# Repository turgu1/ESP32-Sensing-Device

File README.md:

# ESP32 Sensing device V2.0

## Updates

(Updated May 31, 2022)

Received the V2.0 PCBs yesterday. First modifications (Not shown on the schematic):

- Led resistors (R13, R16): 1 kOhms instead of 220 Ohms (the LEDs are way too bright).
- Thermistor 10 kOhms resistor R11 hooked to GPIO25 instead of 3.3V using a wire: To diminish thermistor heath effect on reading values, the GPIO25 is put high only at thermistor read time.

The thermistor is only used when the device is connected to an external source of power: to get an accurate 3.3v source for thermistor read-outs.

To compensate for the lack of linearity of the ESP32 A2D, a lookup table has been generated and used by the software (ESPHome). See the generator here: `software/lut_gener.ino` Pins 34 and 25 must be connected before using the generator (without the GPIO34 resistor). Must be used for each ESP32 instance (will be different for each ESP32 chip). An example of the generated table can be found here: `software/.freezer_adc_lut.h`.

An ESPHome example of use to sense a Freezer is supplied in `software/freezer.yaml`.

(Updated May 19, 2022)

The new version is ready for production. Here are the modifications from version 1.0:

- Sensors using GPIO 15 (Generic sensor), 25 (thermistor) and 27 (light sensor) migrated to GPIO 32, 34 and 35 respectively
- Added I2C interface
- Added program-controlled led
- All parts are aligned in the same direction onboard, to simplify hand soldering
- The board is 0.6mm larger

(Updated May 18, 2022)

The thermistor and photo-resistor sensors are working well. As they use GPIO 25 and 27 A2D capability (ADC2), the WiFi interface cannot be enabled at the same time the sensors are being read: the ADC2 electronics is shared with the onboard  WiFi capability. An updated version of the device is being prepared to use ADC1 GPIOs instead. (This has been corrected in version 2.0)

(Updated May 17, 2022)

All the trials are positive so far. For R1, instead of 10K, I'm using 2.7M ohms.
Remains the thermistor and photo-resistor sensors to try.

(Updated March 29, 2022)

Initial release.

## Introduction

This is a small footprint ESP32-based sensing device, with the following characteristics:

- 30x28 mm circuit board (30x40 mm with ESP32 antenna)
- Two power modes:
    - Battery (AAx2) (through external battery case)
    - External 5 Volts power support (through power-only Micro USB-B port)
- Battery level monitoring circuit
- Three Sensing ports:
    - Multi-Purpose (configurable through Resistor and Capacitor parts)
    - Thermistor (https://learn.adafruit.com/thermistor/using-a-thermistor)
    - Photoresistor (https://learn.adafruit.com/photocells/using-a-photocell)
- I2C Interface port
- External FTDI port (through a 3-pins [GND, RxD, TxD] port) (https://learn.adafruit.com/ftdi-friend)
- RST / PGM buttons
- Power LED (for external power only)
- Programmable LED
- Designed with KiCAD V6.0.5 (https://www.kicad.org)
- Public Domain

&nbsp;&nbsp;&nbsp;&nbsp;

The choice of components is related to their availability in my inventory. 

## Design Description

Looking at the schematic, you will find here the information related to each subsection present on the device. Some subsections are required, and others are optional depending on your needs.

The electronic component identifiers required for each subsection are listed inside square brackets.

### Required Subsections

- **ESP-WROOM-32** [**U1**] - This is the processor in use on the device.
- **RESET Button** [**SW2**, **R6**, **C1**] - Required to maintain the processor working and do a reset when it is required to take back the control for programming or when the device is not behaving properly.
- **PGM Button** [**SW1**, **R5**] - For programming the processor, the PGM Button must be pressed as the reset button is also pressed, and then released *after* releasing the reset button, such that the processor will be put in program loading. The FTDI interface must be connected to the computer to transmit the new program.
- **FTDI** [**D2**, **J1**] - This is the connection to an external FTDI device that allows for communication between the ESP32 processor and a development PC for program loading and debugging output. Connector's pins are labeled **G** (Ground), **R** (RxD), and **T** (TxD) relative to the ESP32 pinout: The External FTDI GND pin must be connected to **G**, the FTDI RxD pin must be connected to **T**, and the FTDI TxD pin must be connected to **R**. Power must be supplied to the board through AA batteries or an external power supply.

### Optional Subsections

- **AAx2 Battery Connector** [**J2**] - If power is to be supplied with AA batteries, the connector is required. The battery holder wires can also be directly soldered in the through-holes. Please respect the polarity (a '+' sign is present on the board to indicate the positive wire location). **Do not connect any battery if you intend to use an external power supply.**
- **External 5V Power**, [**U2**, **J6**, **D1**, **D3**, **R13**, **C2**, **C3**, **C4**, **C5**] - This is a linear 3.3V regulator circuit, only required when a DC 5 Volts power supply is used. It is expected that the power supply is using a male micro USB-B connector. **Do not implement this subsection if you intend to use batteries.**
- **Voltage Monitoring** [**Q1**, **Q2**, **R1**, **R2**, **R3**, **R4**] - This circuit will allow for reading the 3.3 V power voltage for the device through ADC1_0 internal to the ESP32. If AA batteries are used, it will allow monitoring the battery level to replace them when required. The MOSFET transistor [**Q2**] insure that the circuit will not take a load on the batteries. Must be enabled through [**Q1**] using GPIO17.
- **Generic Sensor Input** [**J3**, **R7**, **R8**, **R9**, **R10**] - This is a port to retrieve some sensor information. The four resistors must be adjusted to consider the kind of sensing to be done (pull-up, pull-down, etc.). Some resistor locations can be used for capacitors if required (e.g. adding an RC circuit). This sensor is connected to GPIO32 (ADC1_4) of the ESP32. The J3 pins are labeled 1: G (Gnd), 2: S (Signal).
- **Heat Sensor** [**J4**, **R11**] - Allow for reading the level of Heat using an external thermistor through an A2D of the processor (ADC1). This sensor is connected to GPIO34 (ADC1_6) of the ESP32. Can be used with another kind of sensor as appropriate. The J4 pins are labeled 1: G (Gnd), 2: Th (Signal).
- **Light Sensor** [**J5**, **R12**] - Allow for reading the level of Heat using an external photoresistor through an A2D of the processor (ADC1). This sensor is connected to GPIO35 (ADC1_7) of the ESP32. Can be used with another kind of sensor as appropriate. The J5 pins are labeled 1: G (Gnd), 2: Li (Signal).
- **I2C Interface** [**J7**, **R14**, **R15**] - Used to connect to external I2C devices (displays, sensors, etc). Connected to the ESP32 through GPIO21 (SDA) and GPIO22 (SCL). The J7 connector offers 3.3v and GND pins. Resistors may have to be adjusted depending on the load. The J7 Pins are labeled 1: G (ground), 2: D (SDA), 3: + (3.3v), 4: C (SCL)
- **Program Controlled LED** [**D4**, **R16**] - Could be useful for debugging purpose. Not a good idea to use it on battery-powered devices. Connected to ESP32 GPIO12. Important: Must be programmed as an output GPIO.

### Some potential issues

- The thermistor and photoresistive interfaces are exploratory. The known lack of linearity of the ESP32 A2D may have an impact on the quality of the retrieved data. See [here](https://www.e-tinkers.com/2019/10/using-a-thermistor-with-arduino-and-unexpected-esp32-adc-non-linearity/), and [here](https://rntlab.com/question/analogread-for-ntc-thermistor/) for further information.

- The Micro USB-B connector is a specific part with only 2 through-hole pins (GND and 5V). See the BOM below for purchase locations. On Amazon, there are 100, 30, and 10 pieces bundles available. A more conventional 5-pins connector may be adapted (physical tweak or modification to the board design).

- The Power LED is for use only with the external power supply and is hooked on the 5v side of the linear regulator. It could have been hooked to the 3.3v side, closer to the ESP32.

- The linear 3.3v regulator capacitors may have to be different than the one selected. In particular, on the output side, to get a better transient response, a 22uF tantalum may replace the one indicated (per the AMS1117 spec sheet).

- Using batteries to power the device: depending on the processor speed and the networking requirements at startup (WiFi, BT, BLE), the AA batteries may not be able to supply the required startup current (100 to 500 mA). Many options are possible: use larger batteries, lithium instead of alkaline, and add some capacitors (tantalum or other) at C4/C5 locations.

## Bill of Material (BOM)

| Reference(s) | Value | Footprint | Where to find |
|:------------:|:-----:|:---------:|:--------------|
| C1           | .1uF  | 0805      |               |
| C2, C5       | 10uF  | 0805      |               |
| C3, C4       | 100nF | 0805      |               |
| D1           | MBR120VLSF or equivalent | SOD-123 | [e-Radionica](https://e-radionica.com/en/schottky-diode-mbr120vlsft3g-sod123.html), [Digikey](https://www.digikey.com/en/products/detail/on-semiconductor/MBR120VLSFT3G/1477157), [Mouser](https://www.mouser.com/ProductDetail/onsemi/MBR120VLSFT3G?qs=3JMERSakebrD2yr9jFliaA%3D%3D) |
| D2 | 1N4148WS | SOD-323 | [Digikey](https://www.digikey.com/en/products/detail/on-semiconductor/1N4148WS/1873805), [Mouser](https://www.mouser.ca/ProductDetail/onsemi-Fairchild/1N4148WS?qs=2%2FYqgE%252BHg%252BKBrKZlAsMLhw%3D%3D) |
| D3, D4 | LED | 0805 | |
| J1 | Connector 1x3 | Pin Header 2.54mm | |
| J2, J3, J4, J5 | Connector 1x2 | Pin Header 2.54mm | |
| J6 | Micro-B USB | | [AliExpress](https://fr.aliexpress.com/item/32886396127.html?gatewayAdapt=glo2fra), [Amazon](https://www.amazon.com/uxcell-100PCS-Connector-Replacement-Adapter/dp/B07R1HG29D/ref=psdc_172544_t1_B07R1HRM1T) |
| J7 | Connector 1x4 | Pin Header 2.54mm | |
| Q1 | MMBT3904 | SOT-23 | |
| Q2 | NDS356AP or IRLML5103TRPBF or equivalent | SOT-23 | |
| R1, R3 to R7, R10 to R12 | 10k ohms | 0805 | |
| R2 | 1k ohms | 0805 | |
| R8, R9 | 0 ohms | 0805 | |
| R13, R16 | 220 ohms | 0805 | |
| R14, R15 | 3.3k ohms | 0805 | |
| SW1, SW2 | PTS526_SK15_SMTR2_LFS | SMTR2 | [Mouser](https://www.mouser.com/ProductDetail/CK/PTS526-SK15-SMTR2-LFS?qs=UXgszm6BlbF5Ezp94JAQtw%3D%3D), [Digikey](https://www.digikey.com/en/products/detail/c-k/PTS526-SK15-SMTR2-LFS/10056626), [e-Radionica](https://e-radionica.com/en/smd-pushbutton.html) |
| U1 | ESP-WROOM-32 | | [e-Radionica](https://e-radionica.com/en/esp32-wroom-32d-wifi-module.html) |
| U2 | AMS1117-3.3 | SOT-223-3 | |

## Copyright (c) 2022 Guy Turcotte

Permission is hereby granted, free of charge, to any person obtaining a copy of this project and associated documentation files (the "Project Content"), to deal in the Project without restriction, including without limitation the rights to use, copy, modify, merge, publish, distribute, sublicense, and/or sell copies of the Project Content, and to permit persons to whom the Project Content is furnished to do so, subject to the following conditions:

The above copyright notice and this permission notice shall be included in all copies or substantial portions of the Project Content.

THE PROJECT CONTENT IS PROVIDED "AS IS", WITHOUT WARRANTY OF ANY KIND, EXPRESS OR IMPLIED, INCLUDING BUT NOT LIMITED TO THE WARRANTIES OF MERCHANTABILITY, FITNESS FOR A PARTICULAR PURPOSE, AND NON-INFRINGEMENT. IN NO EVENT SHALL THE AUTHORS OR COPYRIGHT HOLDERS BE LIABLE FOR ANY CLAIM, DAMAGES, OR OTHER LIABILITY, WHETHER IN AN ACTION OF CONTRACT, TORT OR OTHERWISE, ARISING FROM, OUT OF OR IN CONNECTION WITH THE PROJECT CONTENT OR THE USE OR OTHER DEALINGS IN THE PROJECT CONTENT.

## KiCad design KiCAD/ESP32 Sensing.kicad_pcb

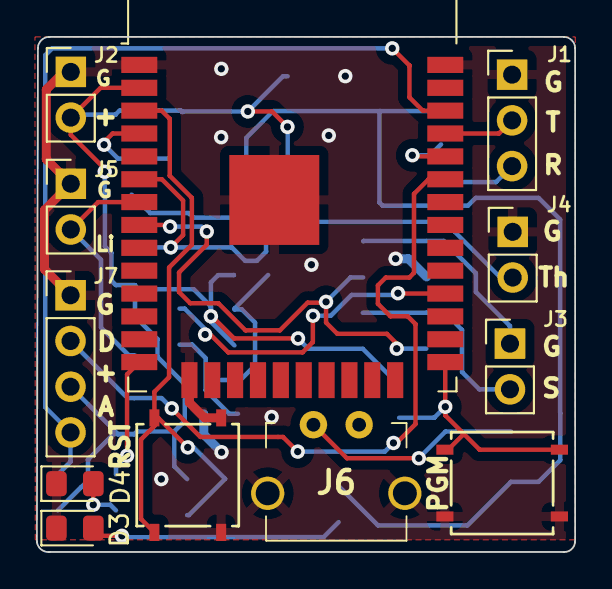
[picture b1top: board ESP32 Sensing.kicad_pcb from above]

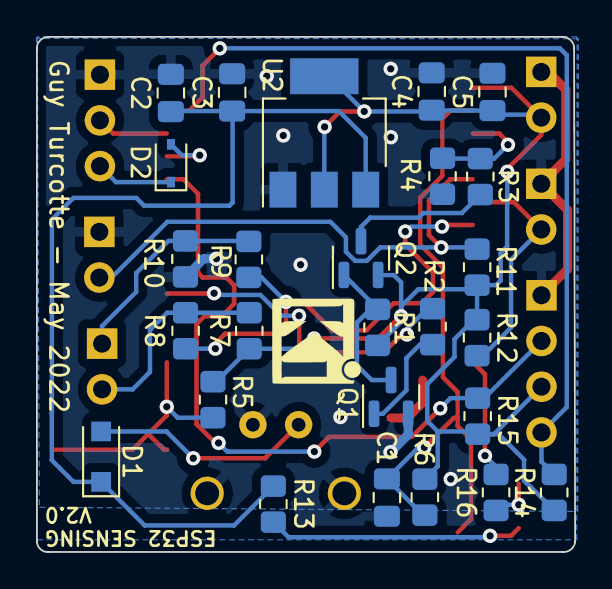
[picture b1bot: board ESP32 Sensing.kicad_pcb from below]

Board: 2 copper layers, 29.9 x 28.6 mm, 38 parts (26 on the bottom side), 24 nets.

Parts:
C1: .1u; C_0805_2012Metric_Pad1.18x1.45mm_HandSolder
C2, C5: 10u; C_0805_2012Metric_Pad1.18x1.45mm_HandSolder
C3, C4: 100n; C_0805_2012Metric_Pad1.18x1.45mm_HandSolder
D1: MBR120VLSF; D_SOD-123F
D2: 1N4148WS; D_SOD-323
D3, D4: LED; LED_0805_2012Metric_Pad1.15x1.40mm_HandSolder
J1: PinHeader_1x03_P2.54mm_Vertical
J2: Ext Battery 3.3V; PinHeader_1x02_P2.54mm_Vertical
J3: Sensor; PinHeader_1x02_P2.54mm_Vertical
J4: Thermistor; PinHeader_1x02_P2.54mm_Vertical
J5: Light Detect; PinHeader_1x02_P2.54mm_Vertical
J6: MICRO-B USB; MICRO-B_USB_POWER
J7: Conn_01x04_Male; PinHeader_1x04_P2.54mm_Vertical
Q1: MMBT3904; SOT-23
Q2: NDS356AP; SOT-23
R1: 2M7; R_0805_2012Metric_Pad1.20x1.40mm_HandSolder
R2: 1k; R_0805_2012Metric_Pad1.20x1.40mm_HandSolder
R3, R4, R5, R6, R7, R10, R11, R12: 10k; R_0805_2012Metric_Pad1.20x1.40mm_HandSolder
R8, R9: 0; R_0805_2012Metric_Pad1.20x1.40mm_HandSolder
R13, R16: 220; R_0805_2012Metric_Pad1.20x1.40mm_HandSolder
R14, R15: 3K3; R_0805_2012Metric_Pad1.20x1.40mm_HandSolder
SW1: PTS526_SK15_SMTR2_LFS
SW2: PTS526_SK15_SMTR2_LFS
U1: ESP32-WROOM-32
U2: AMS1117-3.3; SOT-223-3_TabPin2

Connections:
+3V3: C4.1, C5.1, J2.2, J7.3, Q2.2 (S), R1.1, R5.1, R6.1, R7.2, R11.1, R12.1, R14.1, R15.1, U1.2 (VDD), U2.2 (VO)
A2D: R3.1, R4.2, U1.4 (SENSOR_VP)
EN: C1.1, R6.2, SW2.2, U1.3 (EN)
GND: C1.2, C2.2, C3.2, C4.2, C5.2, D3.1 (K), D4.1 (K), J1.1, J2.1, J4.1, J5.1, J6.2 (GND), J6.3 (Shield), J7.1, Q1.2 (E), R4.1, R10.2, SW1.1, SW2.1, U1.1 (GND), U1.15 (GND), U1.38 (GND), U1.39 (GND), U2.1 (GND)
GPIO12: R16.2, U1.14 (IO12)
GPIO17: R2.1, U1.28 (IO17)
GPIO32: R8.2, R9.2, U1.8 (IO32)
GPIO34: J4.2, R11.2, U1.6 (IO34)
GPIO35: J5.2, R12.2, U1.7 (IO35)
IO0: R5.2, SW1.2, U1.25 (IO0)
unnamed: C2.1, C3.1, D1.1 (K), R13.1, U2.3 (VI)
unnamed: D1.2 (A), J6.1 (5V)
unnamed: D2.1 (K), J1.3
unnamed: D3.2 (A), R13.2
unnamed: D4.2 (A), R16.1
unnamed: J3.1, R9.1, R10.1
unnamed: J3.2, R7.1, R8.1
unnamed: Q1.1 (B), R2.2
unnamed: Q1.3 (C), Q2.1 (G), R1.2
unnamed: Q2.3 (D), R3.2
RxD: D2.2 (A), U1.34 (RXD0/IO3)
SCL: J7.4, R14.2, U1.36 (IO22)
SDA: J7.2, R15.2, U1.33 (IO21)
TxD: J1.2, U1.35 (TXD0/IO1)

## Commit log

2022-03-23 Folders Re-org
2022-03-23 Readme update
2022-03-23 Add Gerber
2022-03-23 Documentation update
2022-03-24 Some symbol adjustments
2022-03-24 Readme adjustment
2022-03-25 Links
2022-03-25 equivalencies
2022-03-25 Date update
2022-03-28 Doc update
2022-03-28 Modified linear regulator capacitor values
2022-05-18 README Update. Added Battery level test.
2022-05-19 Version 2.0
2022-05-19 Updated Gerber files
2022-05-31 Added software examples. Readme update.
